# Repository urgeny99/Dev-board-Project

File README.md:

Honestly I have no idea what i can do with this DevBoard and I did it because it sounded cool and wanted to get KiCad better to know and what you do with all different functions. I hope that all the time I spent building it is worth it in the end. I have to do some research to learn what i can use the devboard for :)

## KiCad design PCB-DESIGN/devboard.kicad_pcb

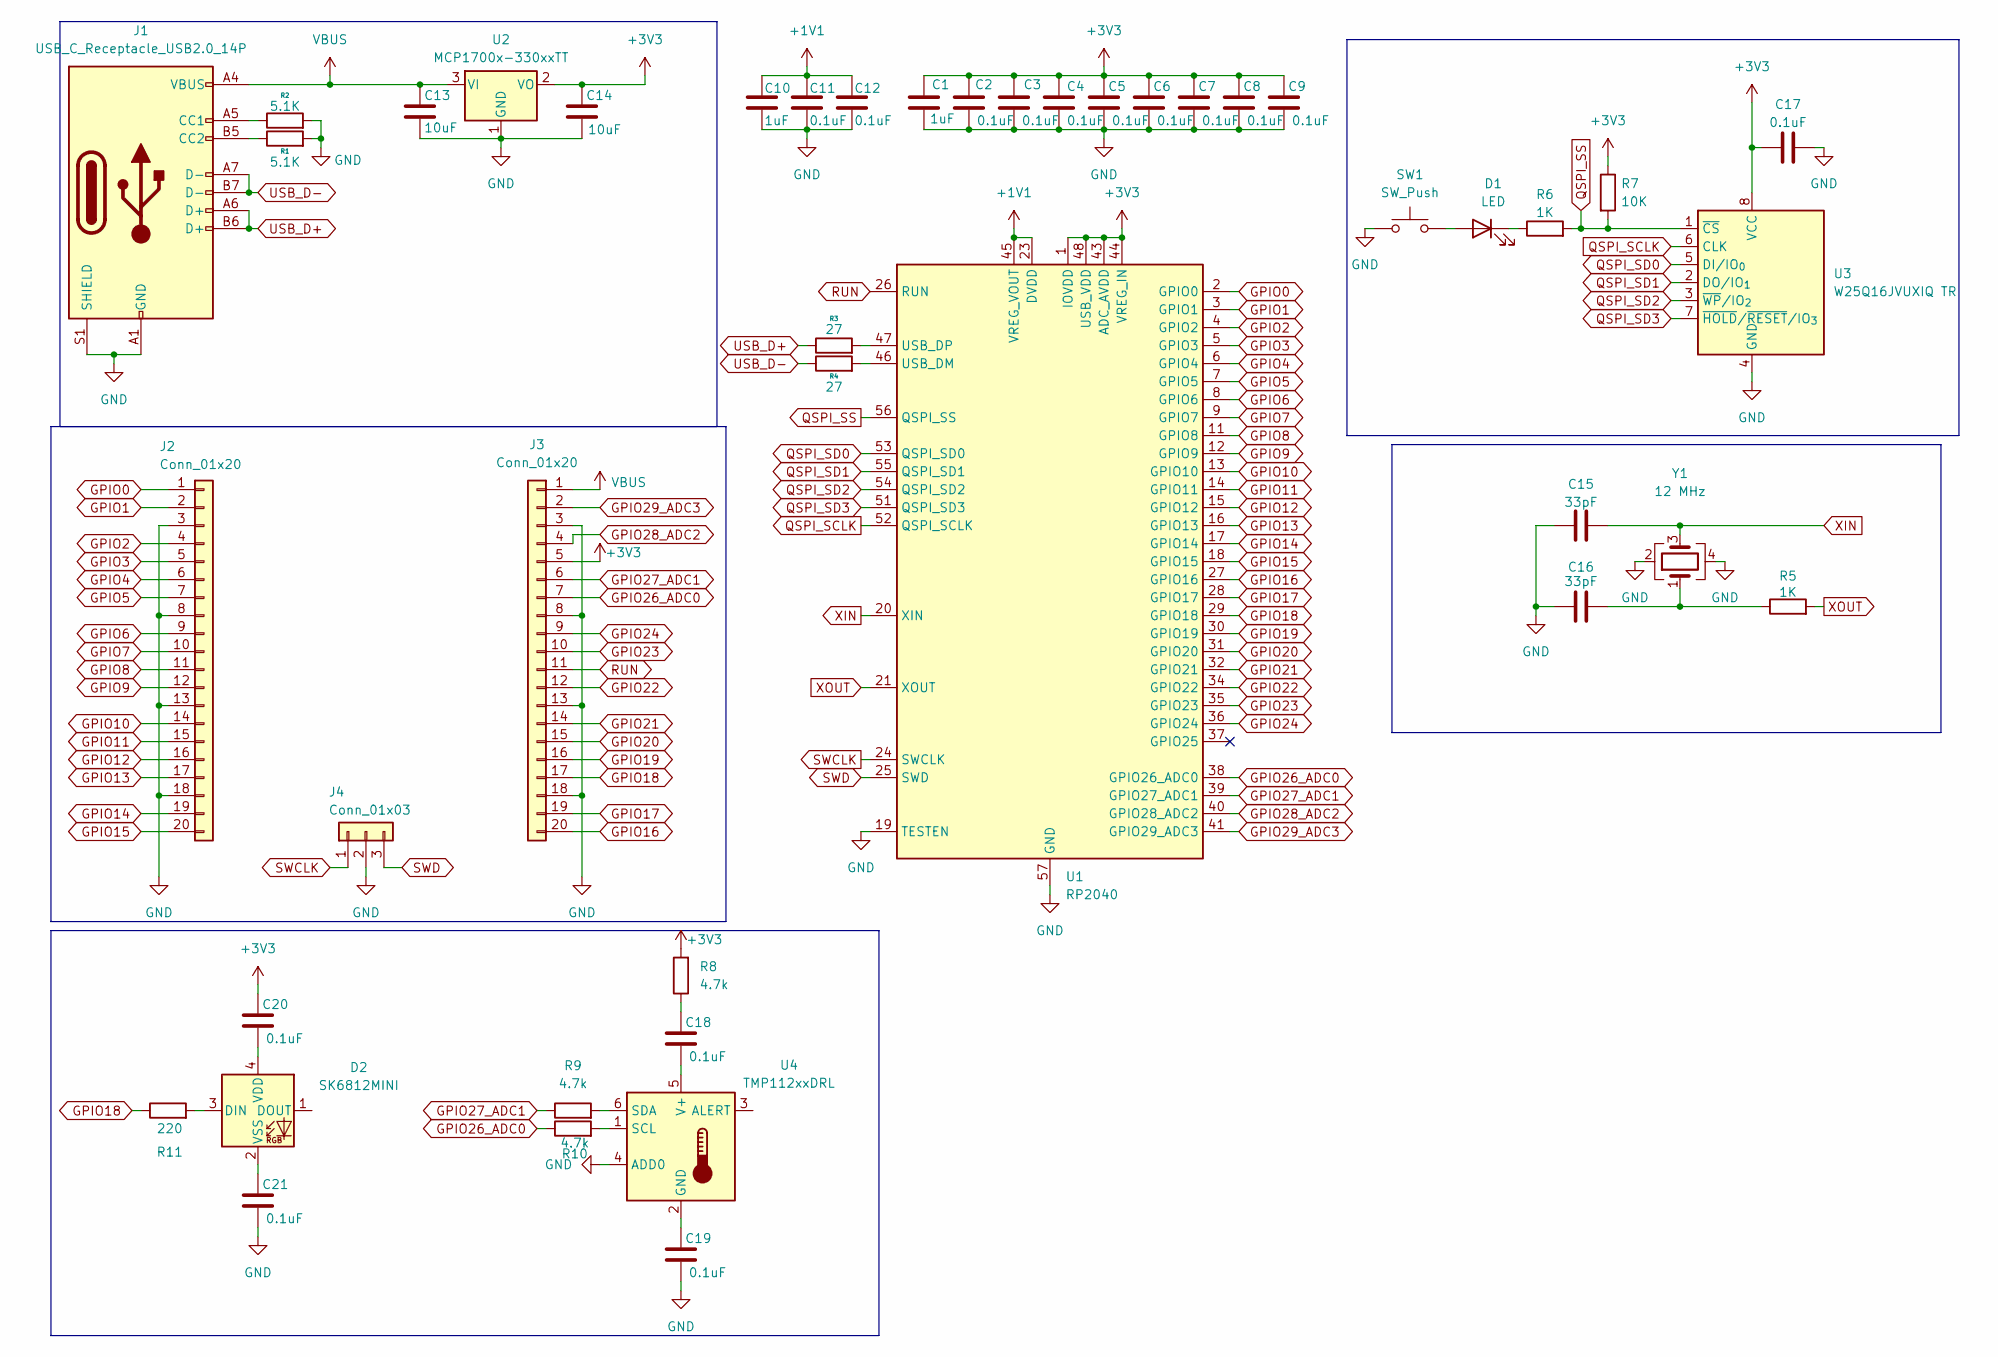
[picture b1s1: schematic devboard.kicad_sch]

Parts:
C1, C10: 1uF; C_0402_1005Metric
C2, C3, C4, C5, C6, C7, C8, C9, C11, C12, C17, C18, C19, C20, C21: 0.1uF; C_0402_1005Metric
C13, C14: 10uF; C_0603_1608Metric
C15, C16: 33pF; C_0402_1005Metric
D1: LED; LED_0402_1005Metric
D2: SK6812MINI; LED_SK6812MINI_PLCC4_3.5x3.5mm_P1.75mm
J1: USB_C_Receptacle_USB2.0_14P; USB_C_Receptacle_HRO_TYPE-C-31-M-12
J2, J3: Conn_01x20; PinHeader_1x20_P2.54mm_Vertical
J4: Conn_01x03; PinHeader_1x03_P2.54mm_Vertical
R1, R2: 5.1K; R_0402_1005Metric
R3, R4: 27; R_0402_1005Metric
R5, R6: 1K; R_0402_1005Metric
R7: 10K; R_0402_1005Metric
R8, R9, R10: 4.7k; R_0402_1005Metric
R11: 220; R_0402_1005Metric
SW1: SW_Push; SW_Push_SPST_NO_Alps_SKRK
U1: RP2040; QFN-56-1EP_7x7mm_P0.4mm_EP3.2x3.2mm
U2: MCP1700x-330xxTT; SOT-23
U3: W25Q16JVUXIQ TR; Winbond_USON-8-1EP_3x2mm_P0.5mm_EP0.2x1.6mm
U4: TMP112xxDRL; SOT-563
Y1: 12 MHz; Crystal_SMD_3225-4Pin_3.2x2.5mm

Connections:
+1V1: C10.1, C11.1, C12.1, U1.23 (DVDD), U1.45 (VREG_VOUT), U1.50 (DVDD)
+3V3: C1.1, C2.1, C3.1, C4.1, C5.1, C6.1, C7.1, C8.1, C9.1, C14.1, C17.1, C20.1, J3.5, R7.1, R8.2, U1.1 (IOVDD), U1.10 (IOVDD), U1.22 (IOVDD), U1.33 (IOVDD), U1.42 (IOVDD), U1.43 (ADC_AVDD), U1.44 (VREG_IN), U1.48 (USB_VDD), U1.49 (IOVDD), U2.2 (VO), U3.8 (VCC)
GND: C1.2, C2.2, C3.2, C4.2, C5.2, C6.2, C7.2, C8.2, C9.2, C10.2, C11.2, C12.2, C13.2, C14.2, C15.1, C16.1, C17.2, C19.2, C21.2, J1.A1 (GND), J1.A12 (GND), J1.B1 (GND), J1.B12 (GND), J1.S1 (SHIELD), J2.3, J2.8, J2.13, J2.18, J3.3, J3.8, J3.13, J3.18, J4.2, R1.2, R2.2, SW1.1, U1.19 (TESTEN), U1.57 (GND), U2.1 (GND), U3.4 (GND), U4.4 (ADD0), Y1.2, Y1.4
GPIO0: J2.1, U1.2 (GPIO0)
GPIO1: J2.2, U1.3 (GPIO1)
GPIO2: J2.4, U1.4 (GPIO2)
GPIO3: J2.5, U1.5 (GPIO3)
GPIO4: J2.6, U1.6 (GPIO4)
GPIO5: J2.7, U1.7 (GPIO5)
GPIO6: J2.9, U1.8 (GPIO6)
GPIO7: J2.10, U1.9 (GPIO7)
GPIO8: J2.11, U1.11 (GPIO8)
GPIO9: J2.12, U1.12 (GPIO9)
GPIO10: J2.14, U1.13 (GPIO10)
GPIO11: J2.15, U1.14 (GPIO11)
GPIO12: J2.16, U1.15 (GPIO12)
GPIO13: J2.17, U1.16 (GPIO13)
GPIO14: J2.19, U1.17 (GPIO14)
GPIO15: J2.20, U1.18 (GPIO15)
GPIO16: J3.20, U1.27 (GPIO16)
GPIO17: J3.19, U1.28 (GPIO17)
GPIO18: J3.17, R11.1, U1.29 (GPIO18)
GPIO19: J3.16, U1.30 (GPIO19)
GPIO20: J3.15, U1.31 (GPIO20)
GPIO21: J3.14, U1.32 (GPIO21)
GPIO22: J3.12, U1.34 (GPIO22)
GPIO23: J3.10, U1.35 (GPIO23)
GPIO24: J3.9, U1.36 (GPIO24)
GPIO26_ADC0: J3.7, R10.1, U1.38 (GPIO26_ADC0)
GPIO27_ADC1: J3.6, R9.1, U1.39 (GPIO27_ADC1)
GPIO28_ADC2: J3.4, U1.40 (GPIO28_ADC2)
GPIO29_ADC3: J3.2, U1.41 (GPIO29_ADC3)
unnamed: C16.2, R5.1, Y1.1
unnamed: C18.1, R8.1
unnamed: D1.2 (A), SW1.2
unnamed: D1.1 (K), R6.1
unnamed: D2.3 (DIN), R11.2
unnamed: C20.2, D2.4 (VDD)
unnamed: C21.1, D2.2 (VSS)
unnamed: J1.A5 (CC1), R2.1
unnamed: J1.B5 (CC2), R1.1
unnamed: R4.2, U1.46 (USB_DM)
unnamed: R3.2, U1.47 (USB_DP)
unnamed: C19.1, U4.2 (GND)
unnamed: R10.2, U4.1 (SCL)
unnamed: R9.2, U4.6 (SDA)
unnamed: C18.2, U4.5 (V+)
QSPI_SCLK: U1.52 (QSPI_SCLK), U3.6 (CLK)
QSPI_SD0: U1.53 (QSPI_SD0), U3.5 (DI/IO_{0})
QSPI_SD1: U1.55 (QSPI_SD1), U3.2 (DO/IO_{1})
QSPI_SD2: U1.54 (QSPI_SD2), U3.3 (~WP/IO_{2})
QSPI_SD3: U1.51 (QSPI_SD3), U3.7 (~HOLD/~RESET/IO_{3})
QSPI_SS: R6.2, R7.2, U1.56 (QSPI_SS), U3.1 (~CS)
RUN: J3.11, U1.26 (RUN)
SWCLK: J4.1, U1.24 (SWCLK)
SWD: J4.3, U1.25 (SWD)
USB_D+: J1.A6 (D+), J1.B6 (D+), R3.1
USB_D-: J1.A7 (D-), J1.B7 (D-), R4.1
VBUS: C13.1, J1.A4 (VBUS), J1.A9 (VBUS), J1.B4 (VBUS), J1.B9 (VBUS), J3.1, U2.3 (VI)
XIN: C15.2, U1.20 (XIN), Y1.3
XOUT: R5.2, U1.21 (XOUT)

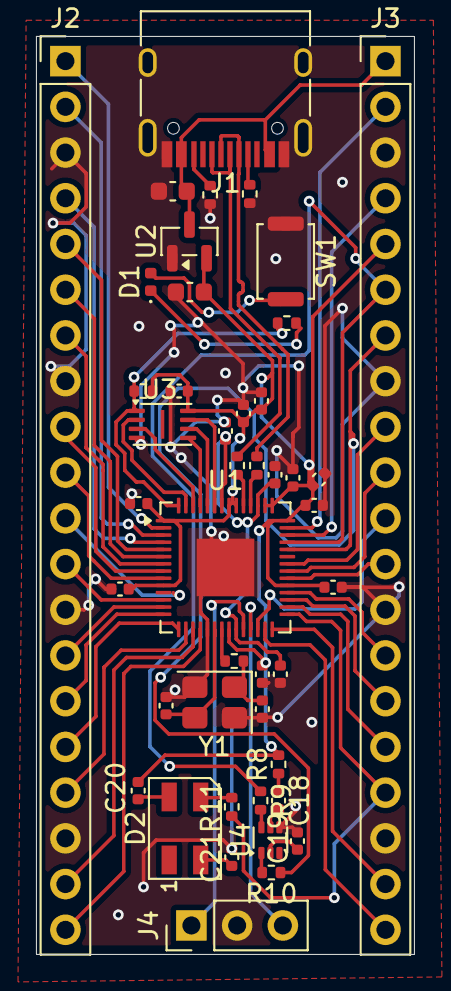
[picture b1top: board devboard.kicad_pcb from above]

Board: 2 copper layers, 21.0 x 51.0 mm, 44 parts (0 on the bottom side), 61 nets.

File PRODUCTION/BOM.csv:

Designator,Footprint,Quantity,Value,JLCPCB Part #,Total Cost
"C1, C10",0402,2,1uF,C52923,€ 0.05
"C11, C12, C17, C2, C3, C4, C5, C6, C7, C8, C9",0402,11,0.1uF,C1525,€ 0.09
"C13, C14",0603,2,10uF,C19702,€ 0.10
"C15, C16",0402,2,33pF,C1562,€ 0.02
D1,0402,1,LED,C965793,€ 0.12
D2,LED_SK6812MINI_PLCC4_3.5x3.5mm_P1.75mm,1,SK6812MINI,C5149201,€ 0.50
J1,USB_C_Receptacle_HRO_TYPE-C-31-M-12,1,USB_C_Receptacle_USB2.0_14P,C165948,€ 0.73
"J2, J3",PinHeader_1x20_P2.54mm_Vertical,2,Conn_01x20,C50981,
J4,PinHeader_1x03_P2.54mm_Vertical,1,Conn_01x03,C24980,
"R1, R2",0402,2,5.1K,C25905,€ 0.01
"R3, R4",0402,2,27,C25100,€ 0.01
"R5, R6",0402,2,1K,C11702,€ 0.01
R7,0402,1,10K,C25744,€ 0.01
"R10, R8, R9",0402,3,4.7k,C25900,€ 0.01
R11,0402,1,220Ω,C25091,€ 0.01
SW1,SW_Push_SPST_NO_Alps_SKRK,1,SW_Push,C720477,€ 0.33
U1,QFN-56-1EP_7x7mm_P0.4mm_EP3.2x3.2mm,1,RP2040,C2040,€ 3.95
U2,SOT-23,1,MCP1700x-330xxTT,C39051,€ 1.70
U3,Winbond_USON-8-1EP_3x2mm_P0.5mm_EP0.2x1.6mm,1,W25Q16JVUXIQ TR,C2843335,€ 2.32
U4,SOT-563,1,TMP112xxDRL,C15999,€ 0.71
Y1,Crystal_SMD_3225-4Pin_3.2x2.5mm,1,12 MHz,C9002,€ 0.51
,,,,,

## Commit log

2025-12-09 Updated ReadMe with my Journal
    Documented the process of creating the DevBoard, including schematic design, component addition, PCB design, and exporting for manufacturing.
2025-12-09 Create Production
2025-12-09 Create PCB_Design
2025-12-09 Create Backups
2025-12-09 Update README with export issues and DevBoard insights
2025-12-09 now my journal
2025-12-09 updated journal
2025-12-09 Created README.md
2025-12-14 Create PCBDESIGN
2025-12-29 Fix typo in Journal.md regarding reviews
